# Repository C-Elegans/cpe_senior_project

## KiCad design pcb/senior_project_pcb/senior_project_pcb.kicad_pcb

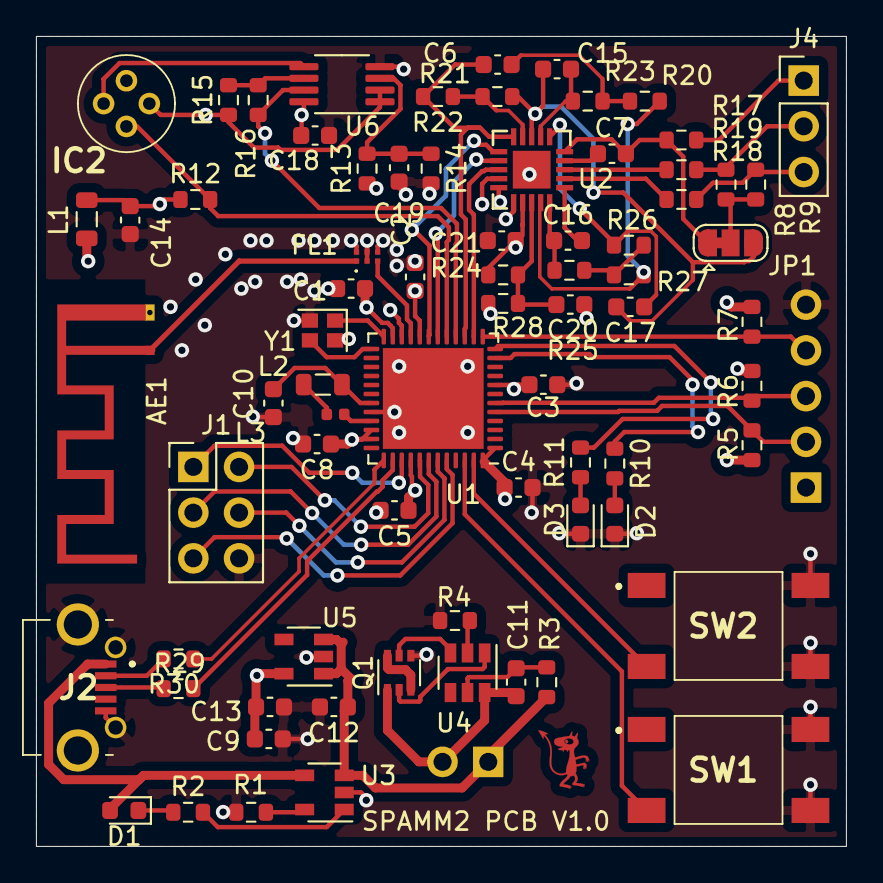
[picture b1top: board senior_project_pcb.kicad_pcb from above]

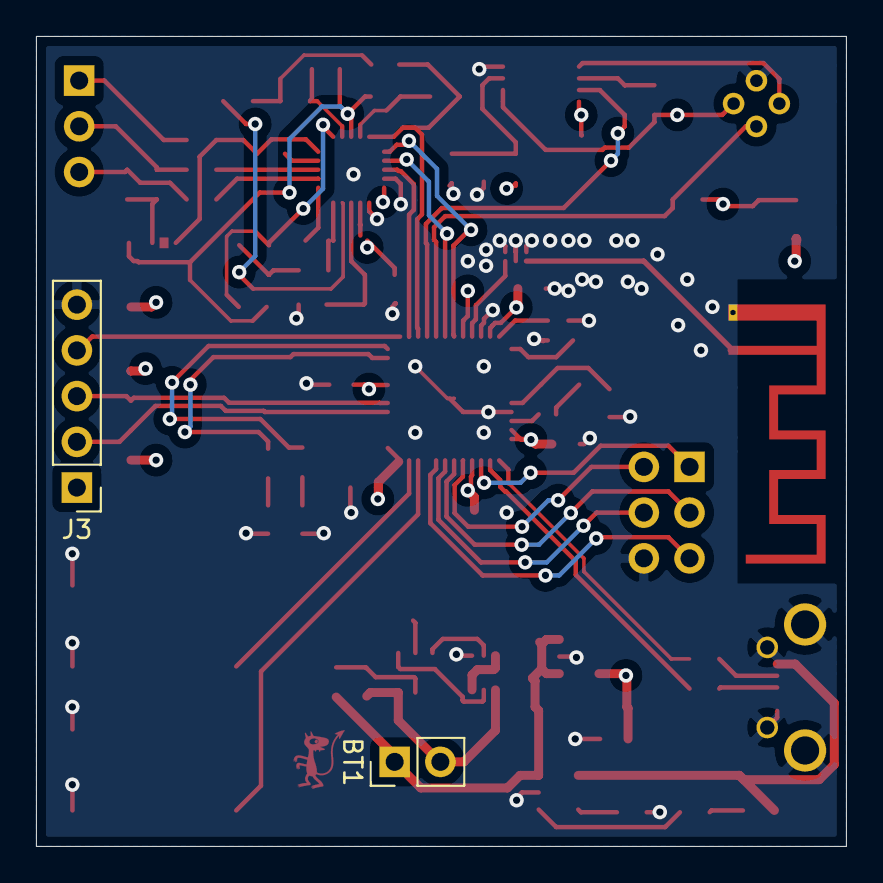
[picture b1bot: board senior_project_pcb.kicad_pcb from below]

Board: 4 copper layers, 45.0 x 45.0 mm, 76 parts (2 on the bottom side), 67 nets.

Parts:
AE1: Antenna_Chip; Texas_SWRA117D_2.4GHz_Left
BT1: Battery_Cell; PinHeader_1x02_P2.54mm_Vertical
C1, C2, C3, C4, C5, C8, C11, C14, C18, C19, C20, C21: 100n; C_0603_1608Metric
C6: 1.5nF; C_0603_1608Metric
C7: 1n; C_0603_1608Metric
C9, C10: 4.7u; C_0603_1608Metric
C12, C13: 1u; C_0603_1608Metric
C15: 10n; C_0603_1608Metric
C16, C17: .33u; C_0603_1608Metric
D1, D2, D3: LED; LED_0603_1608Metric
FL1: MLPF-WB55-01E3; MLPFWB5501E3
IC2: ZTP-148SRC1; ZTP148SRC1
J1: Conn_02x03_Odd_Even; PinHeader_2x03_P2.54mm_Vertical
J2: UJ2-MIBH2-4-SMT-TR; UJ2MIBH24SMTTR
J3: Conn_01x05; PinHeader_1x05_P2.54mm_Vertical
J4: Conn_01x03; PinHeader_1x03_P2.54mm_Vertical
JP1: Jumper_3_Bridged12; SolderJumper-3_P1.3mm_Bridged12_RoundedPad1.0x1.5mm
L1: L_Small; L_0805_2012Metric
L2: 10uH; L_0805_2012Metric
L3: 10n; L_0402_1005Metric
Q1: Q_DUAL_NMOS; SOT-363_SC-70-6
R1: 10k; R_0603_1608Metric
R2: 470; R_0603_1608Metric
R3: 300; R_0603_1608Metric
R4: 2.7k; R_0603_1608Metric
R5, R6, R7: 2k; R_0603_1608Metric
R8, R9, R24, R25, R27, R28: 10M; R_0603_1608Metric
R10, R11: 330; R_0603_1608Metric
R12: 100k 1%; R_0603_1608Metric
R13, R14: 10k 1%; R_0603_1608Metric
R15: 12 1%; R_0603_1608Metric
R16: 33k 1%; R_0603_1608Metric
R17: 360k; R_0603_1608Metric
R18, R19: 180k; R_0603_1608Metric
R20, R22, R23: 1M; R_0603_1608Metric
R21: 100k; R_0603_1608Metric
R26: 1.4M; R_0603_1608Metric
R29, R30: 22; R_0603_1608Metric
SW1, SW2: SW_Push_Dual; LL3301NF065QG
U1: stm32wb55ccu6; QFN-48-1EP_7x7mm_P0.5mm_EP5.6x5.6mm
U2: AD8232ACPZ-R7; LFCSP-20-1EP_4x4mm_P0.5mm_EP2.1x2.1mm
U3: MCP73831-2-OT; SOT-23-5
U4: AP9101CK6; SOT-23-6
U5: MIC5504-3.3YM5; SOT-23-5
U6: AD8539; MSOP-8_3x3mm_P0.65mm
Y1: Crystal_GND24; Crystal_SMD_2016-4Pin_2.0x1.6mm

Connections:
+3.3VA: C3.1, C14.1, C18.1, C21.1, L1.1, R12.1, R13.1, R24.1, U1.8, U2.15, U2.17, U6.8
+3V3: C1.1, C2.1, C4.1, C5.1, C8.1, C9.1, C13.1, J3.1, L1.2, R5.1, R6.1, R7.1, U1.1, U1.20, U1.23, U1.34, U1.35, U1.40, U1.48, U5.5
+BATT: BT1.1, C12.1, R3.1, U3.3, U5.1, U5.3
-BATT: BT1.2, C11.1, Q1.1, U4.6
/ECG_OUT: C6.2, R22.2, U1.15, U2.10
/ECG_SDN: U1.14, U2.13
/INT: J3.4, R7.2, U1.13
/LO+: U1.18, U2.12
/LO-: U1.19, U2.11
/SCL: J3.2, R5.2, U1.5
/SDA: J3.3, R6.2, U1.6
/Temperature Sensor/VGND: IC2.3, R15.1, U6.1, U6.2
/USB_D+: R29.1, U1.38
/USB_D-: R30.2, U1.37
/ecg/LA: J4.3, R9.1, R18.2
/ecg/RA: J4.2, R8.1, R19.2
/ecg/REF: JP1.2, R8.2, R9.2
/ecg/REFOUT: C15.2, C17.2, JP1.3, R21.1, U2.8
/ecg/RL: J4.1, R17.2
/ecg/RLD: C7.2, JP1.1, R17.1, U2.5
/io/BTN1: SW1.3, U1.46
/io/BTN2: SW2.3, U1.47
/io/JTAG_NTRST: J1.5, U1.44
/io/JTAG_TCK: J1.2, U1.41
/io/JTAG_TDI: J1.3, U1.42
/io/JTAG_TDO: J1.4, U1.43
/io/JTAG_TMS: J1.1, U1.39
/io/LED1: R10.1, U1.11
/io/LED2: R11.1, U1.12
/rf/Tline: FL1.3, U1.21
/rf/TlineANT: AE1.1, FL1.1
/thermistor: IC2.2, R12.2, U1.17
/thermopile: R16.1, U1.16, U6.7
GND: AE1.2, C1.2, C2.2, C3.2, C4.2, C5.2, C8.2, C9.2, C10.2, C12.2, C13.2, C14.2, C18.2, C19.2, C20.2, C21.2, D2.1, D3.1, FL1.2, FL1.4, FL1.5, FL1.6, IC2.1, J1.6, J2.5, J2.MH1, J2.MH2, J2.MH3, J2.MH4, J3.5, Q1.4, R1.2, R4.2, R14.2, R28.1, SW1.2, SW1.4, SW2.2, SW2.4, U1.22, U1.32, U1.49, U2.14, U2.16, U2.21, U3.2, U5.2, U6.4, Y1.2, Y1.4
unnamed: C6.1, R20.1, R23.2
unnamed: C7.1, U2.4
unnamed: C10.1, L2.1, U1.31
unnamed: C11.2, R3.2, U4.5
unnamed: C15.1, R23.1, U2.7
unnamed: C16.1, R25.2, U2.20
unnamed: C16.2, U2.1
unnamed: C17.1, R26.2, U2.6
unnamed: C19.1, R13.2, R14.1, U6.3
unnamed: C20.1, R24.2, R28.2, U2.18
unnamed: D1.1, R2.1
unnamed: D2.2, R10.2
unnamed: D3.2, R11.2
unnamed: IC2.4, U6.5
unnamed: J2.2, R30.1
unnamed: J2.3, R29.2
unnamed: L2.2, L3.2
unnamed: L3.1, U1.33
unnamed: Q1.2, U4.1
unnamed: Q1.3, Q1.6
unnamed: Q1.5, U4.3
unnamed: R1.1, U3.5
unnamed: R2.2, U3.1
unnamed: R4.1, U4.2
unnamed: R15.2, R16.2, U6.6
unnamed: R18.1, U2.2
unnamed: R19.1, U2.3
unnamed: R20.2, R27.1, U2.19
unnamed: R21.2, R22.1, U2.9
unnamed: R25.1, R26.1, R27.2
unnamed: U1.24, Y1.1
unnamed: U1.25, Y1.3
VBUS: D1.2, J2.1, U3.4

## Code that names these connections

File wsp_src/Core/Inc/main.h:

/* USER CODE BEGIN Header */
/**
  ******************************************************************************
  * @file           : main.h
  * @brief          : Header for main.c file.
  *                   This file contains the common defines of the application.
  ******************************************************************************
  * @attention
  *
  * <h2><center>&copy; Copyright (c) 2021 STMicroelectronics.
  * All rights reserved.</center></h2>
  *
  * This software component is licensed by ST under BSD 3-Clause license,
  * the "License"; You may not use this file except in compliance with the
  * License. You may obtain a copy of the License at:
  *                        opensource.org/licenses/BSD-3-Clause
  *
  ******************************************************************************
  */
/* USER CODE END Header */

/* Define to prevent recursive inclusion -------------------------------------*/
#ifndef __MAIN_H
#define __MAIN_H

#ifdef __cplusplus
extern "C" {
#endif

/* Includes ------------------------------------------------------------------*/
#include "stm32wbxx_hal.h"

/* Private includes ----------------------------------------------------------*/
/* USER CODE BEGIN Includes */
#include "FreeRTOS.h"
#include "cmsis_os.h"
/* USER CODE END Includes */

/* Exported types ------------------------------------------------------------*/
/* USER CODE BEGIN ET */

/* USER CODE END ET */

/* Exported constants --------------------------------------------------------*/
/* USER CODE BEGIN EC */

/* USER CODE END EC */

/* Exported macro ------------------------------------------------------------*/
/* USER CODE BEGIN EM */
extern TIM_HandleTypeDef htim2;
extern ADC_HandleTypeDef hadc1;
extern I2C_HandleTypeDef hi2c1;
extern osThreadId_t max30102TaskHandle;
extern volatile uint8_t notify_button_value;
/* USER CODE END EM */

/* Exported functions prototypes ---------------------------------------------*/
void Error_Handler(void);

/* USER CODE BEGIN EFP */
void SystemClock_Config(void);

/* USER CODE END EFP */

/* Private defines -----------------------------------------------------------*/
#define LED1_Pin GPIO_PIN_2
#define LED1_GPIO_Port GPIOA
#define LED2_Pin GPIO_PIN_3
#define LED2_GPIO_Port GPIOA
#define SPO2_INT_Pin GPIO_PIN_4
#define SPO2_INT_GPIO_Port GPIOA
#define SPO2_INT_EXTI_IRQn EXTI4_IRQn
#define ECG_SDN_Pin GPIO_PIN_5
#define ECG_SDN_GPIO_Port GPIOA
#define ECG_OUT_Pin GPIO_PIN_6
#define ECG_OUT_GPIO_Port GPIOA
#define THERMOPILE_Pin GPIO_PIN_7
#define THERMOPILE_GPIO_Port GPIOA
#define THERMISTOR_Pin GPIO_PIN_8
#define THERMISTOR_GPIO_Port GPIOA
#define LO_P_Pin GPIO_PIN_9
#define LO_P_GPIO_Port GPIOA
#define LO_N_Pin GPIO_PIN_2
#define LO_N_GPIO_Port GPIOB
#define BTN1_Pin GPIO_PIN_6
#define BTN1_GPIO_Port GPIOB
#define BTN1_EXTI_IRQn EXTI9_5_IRQn
#define BTN2_Pin GPIO_PIN_7
#define BTN2_GPIO_Port GPIOB
#define BTN2_EXTI_IRQn EXTI9_5_IRQn
/* USER CODE BEGIN Private defines */

/* USER CODE END Private defines */

#ifdef __cplusplus
}
#endif

#endif /* __MAIN_H */

/************************ (C) COPYRIGHT STMicroelectronics *****END OF FILE****/

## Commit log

2020-11-23 Add Core
2020-11-23 Add Drivers
2020-11-23 Add Middlewares
2020-11-23 Add rest of project files
2020-11-23 Add PCB files
2021-01-26 Move Microcontroller sources to own folder
2021-01-26 Have ConnectionSettings show the available serial ports
2021-01-26 Add GTK+ Hello world example
2021-01-26 Add skeleton desktop app
2021-01-26 Add window to select the serial port
2021-01-26 Have ConnectionSettingsDialog create a connection settings object for the main app
2021-01-26 Add dispatcher and thread
2021-01-26 Fix app crashing if /dev/serial/by-id/ is not present
2021-01-26 Fixed linking gtkmm on mac
2021-01-27 Add pulse oximeter circuit
2021-01-27 Connect up the pulse oximeter and USB
2021-01-27 Add buttons and LEDs
2021-02-02 Add temp sensor
2021-02-02 Start addition of mac serial ports
2021-02-11 Fix things not working on mac
2021-02-11 Fix defines for linux
2021-02-11 Add asan flags for debug builds
2021-02-16 Initial layout mostly done
2021-02-18 Add ecg sensor
2021-02-21 Add RF/Bluetooth to PCB
2021-02-23 PCB Update
2021-02-25 Send PCB off for manufacture
2021-03-03 Add ADC interrupt (not working though)
2021-03-03 Add ADC end of conversion interrupt example
2021-03-03 Add comments
2021-03-06 Add project for STM32WB55 MCU
2021-03-06 Add FreeRTOS and example code
2021-03-10 Begin testing the PCB
2021-03-10 Enable SMPS
2021-03-10 USB Working, enable and print ADC
2021-03-10 Add thermistor calculations
2021-03-16 Added correct thermopile calculations
2021-03-17 Enable timer 2 interrupt
2021-03-18 Add in paul's changes for I2C
2021-03-23 Add ECG Circular Buffer Data Collection
2021-03-23 Add CMSIS DSP Library
2021-03-25 Add FIR filter coefficients and machinery
2021-03-25 Add code to blink the LED in morse code
2021-03-25 Begin work on menu system
2021-03-30 Add menu state machine
2021-04-05 ECG testing branch
2021-04-06 Fix completely borked include paths
2021-04-06 Doing some ECG testing, trying to print (float32_t)filter_output
2021-04-06 Add tab pane to main window of desktop app
2021-04-06 Begin adding tabs for ECG and Temperature
2021-04-06 add pcb gitignore
2021-04-06 Add temperature history list to temperature tab
2021-04-06 Made the buffer printing better
2021-04-07 Remove ASAN
2021-04-08 Added DAS
2021-04-08 Fix build errors in dafu.c
2021-04-10 Add ability to read from USB VCP
2021-04-10 Add interface to have das print data from USB
2021-04-10 Add method to get a temperature data point
2021-04-10 Add method to set time interval and items to retrieve
2021-04-10 Work on retrieving data via the desktop app
2021-04-10 Successfully read temperature data from device and display in GUI
2021-04-10 Sort the temperature column
2021-04-10 Fix some errors with the usb buffer interface
2021-04-10 Make the thing work more reliably
2021-04-11 Initial Branch Commit
2021-04-11 algorithm
2021-04-11 Test
    Can you try testing this code Michael?
2021-04-11 Fast mode?
2021-04-11 Fix SPO2 sensor not working
2021-04-11 Run task much less often
2021-04-13 Only use glob on mac and linux
2021-04-13 Revert "Only use glob on mac and linux"
    This reverts commit 9ffb3cee24cff7d13f9405d93a9fbda9d11ed410.
2021-04-13 Minor fixes after merge
2021-04-14 Fix getting weird values from filtered output
2021-04-14 Fix segementation fault when no port selected
2021-04-14 Add ECG Task to handle ecg IO and filter running
2021-04-14 Add ability to measure temperature from buttons
2021-04-14 Add ability to start and stop ECG through button menu
2021-04-14 Add ability to start/stop ecg through DAS
2021-04-14 Add graph area to graph ecg output
2021-04-14 Fix layout looking stupid
2021-04-14 Attempt to get it to graph the ecg data
2021-04-14 Fix some bugs
2021-04-15 Create worker thread to read ecg data
2021-04-15 Create working(ish) ecg graph
2021-04-15 Further tweaks to sensor
2021-04-15 Fix weirdness with stopping the ECG
2021-04-15 Fix desktop app on mac
2021-04-15 Add celcius to fahrenheit conversion
2021-04-18 Integrate oximeter operation with DAS
2021-04-18 Add tab for pulse oximeter
2021-04-18 Add support for reading data from oximeter
2021-04-18 Add ability to put system to sleep
2021-04-18 Add sleep and oximeter to button menu
